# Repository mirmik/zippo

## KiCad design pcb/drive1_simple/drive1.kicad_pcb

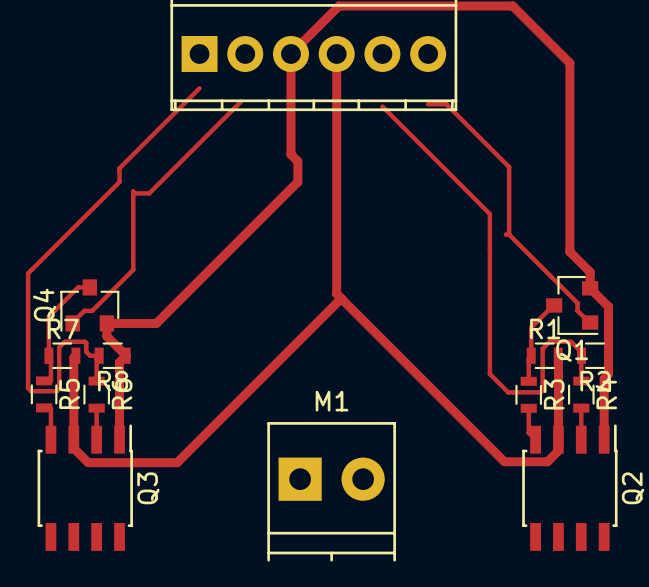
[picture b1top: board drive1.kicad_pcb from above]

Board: 2 copper layers, 14 parts (0 on the bottom side), 14 nets.

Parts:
J1: Screw_Terminal_01x06; TerminalBlock_Phoenix_MPT-2.54mm_6pol
M1: Servo Motor; TerminalBlock_Phoenix_PT-3.5mm_2pol
Q1, Q4: 2N7002; SOT-23
Q2, Q3: IRF7309IPBF; SOIC-8_3.9x4.9mm_Pitch1.27mm
R1, R2, R3, R4, R5, R6, R7, R8: R; R_0603

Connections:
+BATT: J1.4, Q2.3, Q3.3, R1.2, R7.2
/BOT_L: J1.2, R2.2, R4.1
/BOT_R: J1.5, R6.1, R8.2
/MM1: M1.2, Q2.5, Q2.6, Q2.7, Q2.8
/MM2: M1.1, Q3.5, Q3.6, Q3.7, Q3.8
/TOP_L: J1.1, Q1.1
/TOP_R: J1.6, Q4.1
GNDREF: J1.3, Q1.2, Q2.1, Q3.1, Q4.2, R2.1, R8.1
unnamed: Q1.3, R1.1, R3.1
unnamed: Q2.2, R4.2
unnamed: Q2.4, R3.2
unnamed: Q3.2, R6.2
unnamed: Q3.4, R5.2
unnamed: Q4.3, R5.1, R7.1

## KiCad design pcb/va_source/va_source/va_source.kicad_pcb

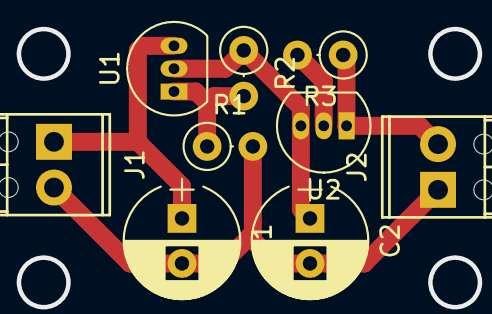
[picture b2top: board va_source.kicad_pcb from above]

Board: 2 copper layers, 9 parts (0 on the bottom side), 6 nets.

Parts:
C1, C2: CP; CP_Radial_D6.3mm_P2.50mm
J1: Power; TerminalBlock_Phoenix_MPT-2.54mm_2pol
J2: Output; TerminalBlock_Phoenix_MPT-2.54mm_2pol
R1, R2, R3: R; R_Axial_DIN0207_L6.3mm_D2.5mm_P2.54mm_Vertical
U1, U2: LM317L_TO92; TO-92_Inline_Narrow_Oval

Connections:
/GND: C1.2, C2.2, J1.2, J2.1, R1.2
unnamed: C1.1, J1.1, U1.3
unnamed: C2.1, R2.1, U1.2, U2.3
unnamed: J2.2, R3.1, U2.1
unnamed: R1.1, R2.2, U1.1
unnamed: R3.2, U2.2

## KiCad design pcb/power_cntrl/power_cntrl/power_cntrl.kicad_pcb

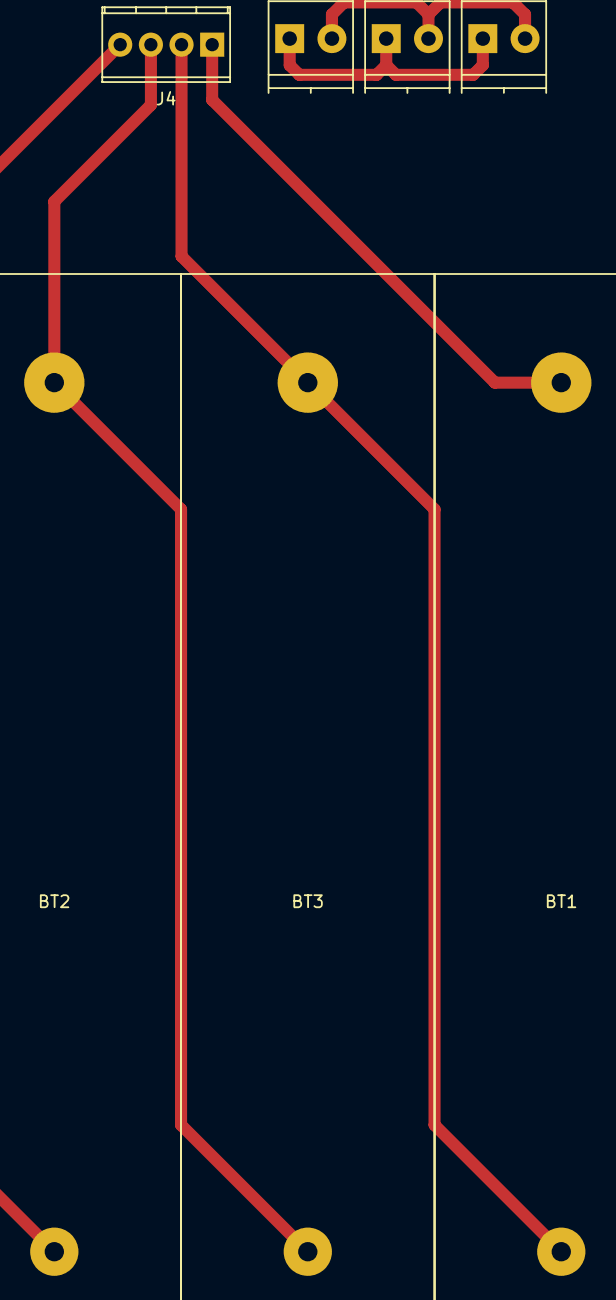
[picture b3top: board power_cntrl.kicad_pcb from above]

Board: 2 copper layers, 7 parts (0 on the bottom side), 6 nets.

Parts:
BT1, BT2, BT3: Battery_Cell; 18650Holder
J1: Conn_01x02_Male; TerminalBlock_Phoenix_PT-3.5mm_2pol
J2, J3: Screw_Terminal_01x02; TerminalBlock_Phoenix_PT-3.5mm_2pol
J4: Conn_01x04_Male; TerminalBlock_Phoenix_MPT-2.54mm_4pol

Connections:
/B1: BT1.1, BT3.2, J4.2
/B2: BT2.2, BT3.1, J4.3
/B+: BT2.1, J4.4
/B-: BT1.2, J4.1
unnamed: J1.1, J2.1, J3.1
unnamed: J1.2, J2.2, J3.2

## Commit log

2018-07-12 __pycache__
2018-08-20 removed *.bin from git
2018-08-20 master squashed
2018-08-20 android
2019-01-13 'vvv'
2019-02-06 'modernize'
2019-05-13 'circle tangent'
2019-05-17 'fix make'
2019-05-25 'c++17'
2019-05-29 'add firmware to gitignore'
2020-07-05 'stereopi'
2020-07-09 'prgrs'
2020-08-20 'xml'
2021-11-01 'clean old headers'
2021-11-03 'warnings'
2021-11-03 Commit maked with world fpush script.
2021-11-23 'allocator'
2021-12-22 '.vscode'
2022-07-10 'compile'
2022-07-11 'add test'
2022-09-29 'add clang-format'
2022-09-29 'upload zippo bonesinger'
2022-10-18 'add make script'
2022-10-19 'rename pipeline scripte'
